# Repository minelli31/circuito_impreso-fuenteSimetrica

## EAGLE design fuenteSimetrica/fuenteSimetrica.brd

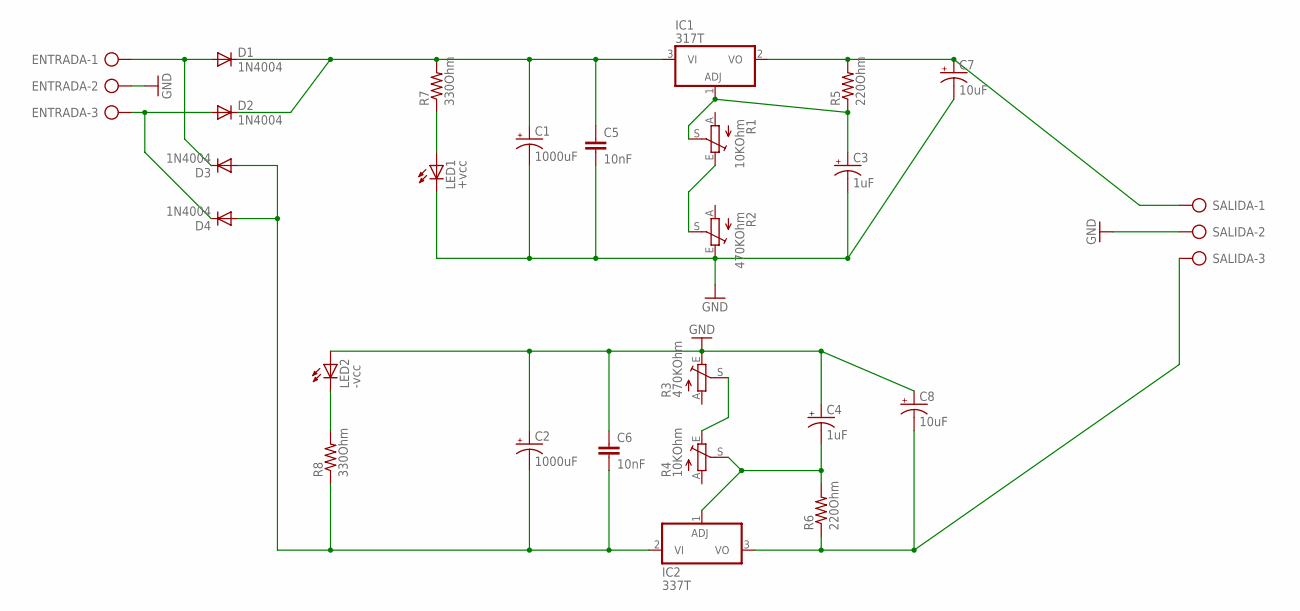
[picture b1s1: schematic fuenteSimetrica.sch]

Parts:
C1, C2: 1000uF; E3,5-8
C3, C4: 1uF; E2,5-6
C5, C6: 10nF; C050-030X075
C7, C8: 10uF; E2,5-6
D1, D2, D3, D4: 1N4004; DO41-10
ENTRADA: AK500/3-H
IC1: 317T; TO220H
IC2: 337T; TO220H
LED1: +vcc; LED5MM
LED2: -vcc; LED5MM
R1, R4: 10KOhm; RS3
R2, R3: 470KOhm; RS3
R5, R6: 220Ohm; 0207/10
R7, R8: 330Ohm; 0207/10
SALIDA: AK500/3-H

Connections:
GND: C1.-, C2.+, C3.-, C4.+, C5.2, C6.1, C7.-, C8.+, ENTRADA.2, LED1.K (C), LED2.A, R2.E, R3.E, SALIDA.2
unnamed: D1.A, D3.C, ENTRADA.1
unnamed: C1.+, C5.1, D1.C, D2.C, IC1.3 (VI), R7.2
unnamed: D2.A, D4.C, ENTRADA.3
unnamed: LED1.A, R7.1
unnamed: C7.+, IC1.2 (VO), R5.2, SALIDA.1
unnamed: R1.E, R2.S
unnamed: LED2.K (C), R8.2
unnamed: C3.+, IC1.1 (ADJ), R1.S, R5.1
unnamed: C4.-, IC2.1 (ADJ), R4.S, R6.2
unnamed: R3.S, R4.E
unnamed: C8.-, IC2.3 (VO), R6.1, SALIDA.3
unnamed: C2.-, C6.2, D3.A, D4.A, IC2.2 (VI), R8.1

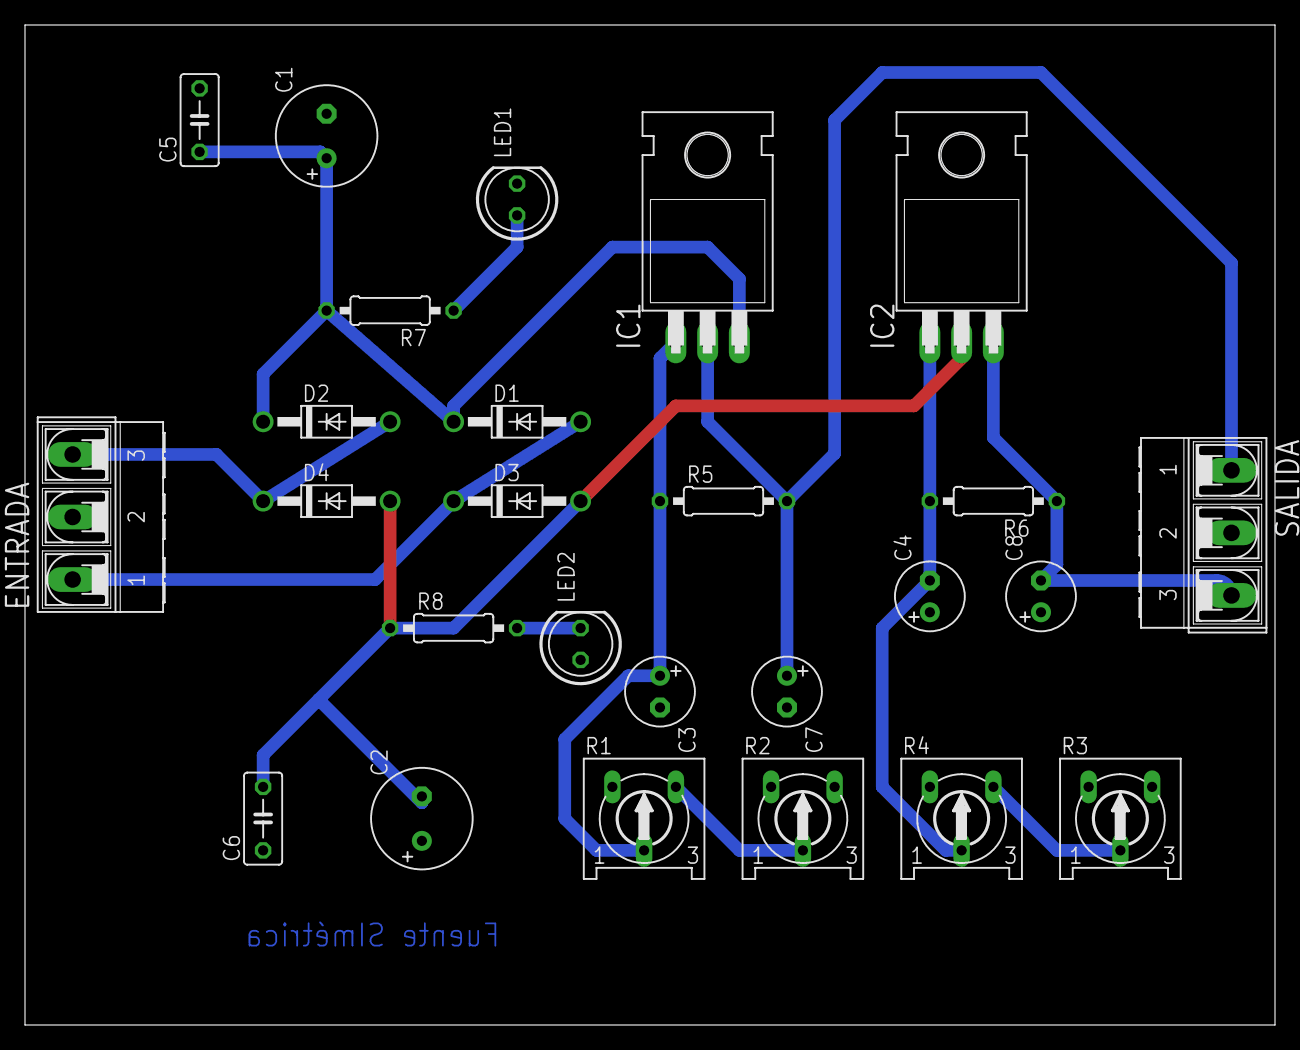
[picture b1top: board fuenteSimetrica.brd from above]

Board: 2 copper layers, 100.0 x 80.0 mm, 26 parts (0 on the bottom side), 13 nets.

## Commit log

2016-07-04 Fuente Simétrica
